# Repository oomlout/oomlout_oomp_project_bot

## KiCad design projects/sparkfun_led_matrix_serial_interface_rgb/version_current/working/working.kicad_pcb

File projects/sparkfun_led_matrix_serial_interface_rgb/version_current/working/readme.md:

# OOMP Project  
## LED_Matrix_Serial_Interface_RGB  by sparkfun  
  
oomp key: oomp_projects_flat_sparkfun_led_matrix_serial_interface_rgb  
(snippet of original readme)  
  
LED Matrix Serial Interface-RGB  
===============================  
  
[    
*LED Matrix - Serial Interface RGB (COM-00760)*](https://www.sparkfun.com/products/760)  
  
This is a large sized RGB LED matrix with a backpack that has been designed to take SPI serial input and display any graphics you pass it.  
  
Repository Contents  
-------------------  
* **/Firmware** - Any firmware that the part ships with,   
* **/Hardware** - All Eagle design files (.brd, .sch, .STL)  

License Information  
-------------------  
The hardware is released under [Creative Commons Share-alike 3.0](http://creativecommons.org/licenses/by-sa/3.0/).    
All other code is open source so please feel free to do anything you want with it; you buy me a beer if you use this and we meet someday ([Beerware license](http://en.wikipedia.org/wiki/Beerware)).  

  full source readme at [readme_src.md](readme_src.md)  
  
source repo at: [https://github.com/sparkfun/LED_Matrix_Serial_Interface_RGB](https://github.com/sparkfun/LED_Matrix_Serial_Interface_RGB)  
## Board  

## Schematic  

[schematic pdf](working_schematic.pdf)  
## Images

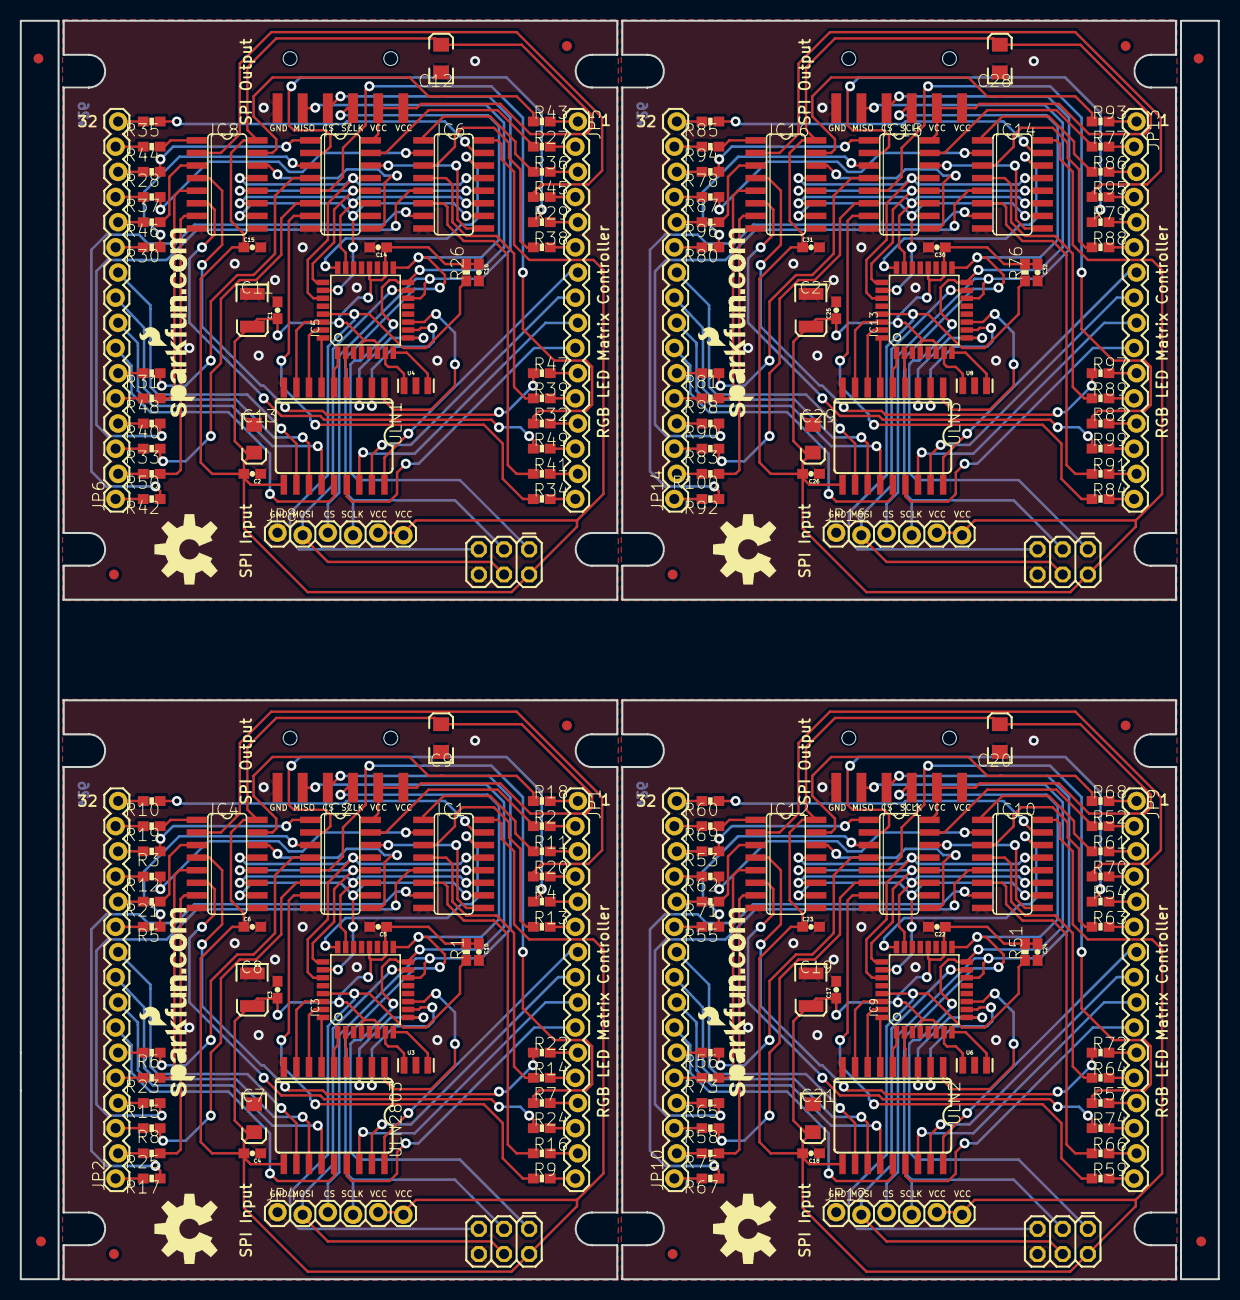
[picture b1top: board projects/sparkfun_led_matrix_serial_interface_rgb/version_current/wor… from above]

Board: 2 copper layers, 120.9 x 127.0 mm, 196 parts (0 on the bottom side), 320 nets.

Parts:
C1, C2, C3, C4, C17, C18, C25, C26: 0.1uf; 0603-CAP
C5, C6, C10, C14, C15, C16, C22, C23, C24, C30, C31, C32: 0.1uF; 0603-CAP
C7, C9, C12, C13, C20, C21, C28, C29: 10uF; EIA3216
C8, C11, C19, C27: 47uF; EIA3528
E$1, E$2, E$3, E$4: FIDUCIAL-1X2
IC1, IC2, IC4, IC6, IC7, IC8, IC10, IC11, IC12, IC14, IC15, IC16: 74LS595D; SO16
IC3, IC5, IC9, IC13: AVR-MEGA8-AI; TQFP32-08
JP1, JP2, JP5, JP6, JP9, JP10, JP13, JP14: M16LOCK; 1X16_LOCK
JP3, JP7, JP11, JP15: 1X06-SMD
JP4, JP8, JP12, JP16: 1X06_LOCK
LOGO1, LOGO2, LOGO3, LOGO4: OSHW-LOGOL; OSHW-LOGO-L
R1, R26, R51, R76: 10k; 0603-RES
R2, R3, R4, R5, R6, R7, R8, R9, R10, R11, R12, R13, R14, R15, R16, R17, R18, R19, R20, R21, R22, R23, R24, R25, R27, R28, R29, R30, R31, R32, R33, R34, R35, R36, R37, R38, R39, R40, R41, R42, R43, R44, R45, R46, R47, R48, R49, R50, R52, R53, R54, R55, R56, R57, R58, R59, R60, R61, R62, R63, R64, R65, R66, R67, R68, R69, R70, R71, R72, R73, R74, R75, R77, R78, R79, R80, R81, R82, R83, R84, R85, R86, R87, R88, R89, R90, R91, R92, R93, R94, R95, R96, R97, R98, R99, R100: 100; 0603-RES
U1, U2, U5, U7: AVR_SPI_PRG_6PTH; 2X3
U3, U4, U6, U8: 16 MHz; RESONATOR-SMD
U$1, U$2, U$3, U$4, U$6, U$7, U$10, U$11: FIDUCIAL1X2; FIDUCIAL-1X2
U$5, U$8, U$9, U$12: SFE-NEW-WEBLOGO
ULN1, ULN2, ULN3, ULN2803: SO18L

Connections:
B1: JP1.1, R18.2
B2: JP2.15, R19.2
B3: JP1.4, R20.2
B4: JP2.12, R21.2
B5: JP1.11, R22.2
B6: JP2.5, R23.2
B7: JP1.14, R24.2
B8: JP2.2, R25.2
B9: JP5.1, R43.2
B10: JP6.15, R44.2
B11: JP5.4, R45.2
B12: JP6.12, R46.2
B13: JP5.11, R47.2
B14: JP6.5, R48.2
B15: JP5.14, R49.2
B16: JP6.2, R50.2
B17: JP9.1, R68.2
B18: JP10.15, R69.2
B19: JP9.4, R70.2
B20: JP10.12, R71.2
B21: JP9.11, R72.2
B22: JP10.5, R73.2
B23: JP9.14, R74.2
B24: JP10.2, R75.2
B25: JP13.1, R93.2
B26: JP14.15, R94.2
B27: JP13.4, R95.2
B28: JP14.12, R96.2
B29: JP13.11, R97.2
B30: JP14.5, R98.2
B31: JP13.14, R99.2
B32: JP14.2, R100.2
CS: IC3.14, JP3.4, JP4.3
CS1: IC5.14, JP7.4, JP8.3
CS2: IC9.14, JP11.4, JP12.3
CS3: IC13.14, JP15.4, JP16.3
G1: JP1.2, R2.2
G2: JP2.14, R3.2
G3: JP1.5, R4.2
G4: JP2.11, R5.2
G5: JP2.6, R6.2
G6: JP1.13, R7.2
G7: JP2.3, R8.2
G8: JP1.16, R9.2
G9: JP5.2, R27.2
G10: JP6.14, R28.2
G11: JP5.5, R29.2
G12: JP6.11, R30.2
G13: JP6.6, R31.2
G14: JP5.13, R32.2
G15: JP6.3, R33.2
G16: JP5.16, R34.2
G17: JP9.2, R52.2
G18: JP10.14, R53.2
G19: JP9.5, R54.2
G20: JP10.11, R55.2
G21: JP10.6, R56.2
G22: JP9.13, R57.2
G23: JP10.3, R58.2
G24: JP9.16, R59.2
G25: JP13.2, R77.2
G26: JP14.14, R78.2
G27: JP13.5, R79.2
G28: JP14.11, R80.2
G29: JP14.6, R81.2
G30: JP13.13, R82.2
G31: JP14.3, R83.2
G32: JP13.16, R84.2
GND: C3.2, C4.1, C5.2, C6.2, C7.C, C8.C, C9.C, C10.2, IC1.8, IC2.8, IC3.3, IC3.5, IC3.21, IC4.8, JP3.6, JP4.1, U2.6, U3.2, ULN2803.9
GND1: C1.2, C2.1, C11.C, C12.C, C13.C, C14.2, C15.2, C16.2, IC5.3, IC5.5, IC5.21, IC6.8, IC7.8, IC8.8, JP7.6, JP8.1, U1.6, U4.2, ULN1.9
GND2: C17.2, C18.1, C19.C, C20.C, C21.C, C22.2, C23.2, C24.2, IC9.3, IC9.5, IC9.21, IC10.8, IC11.8, IC12.8, JP11.6, JP12.1, U5.6, U6.2, ULN2.9
GND3: C25.2, C26.1, C27.C, C28.C, C29.C, C30.2, C31.2, C32.2, IC13.3, IC13.5, IC13.21, IC14.8, IC15.8, IC16.8, JP15.6, JP16.1, U7.6, U8.2, ULN3.9
MISO: IC3.16, JP3.5, U2.1
MISO1: IC5.16, JP7.5, U1.1
MISO2: IC9.16, JP11.5, U5.1
MISO3: IC13.16, JP15.5, U7.1
MOSI: IC3.15, JP4.2, U2.4
MOSI1: IC5.15, JP8.2, U1.4
MOSI2: IC9.15, JP12.2, U5.4
MOSI3: IC13.15, JP16.2, U7.4
unnamed: IC3.7, U3.1
unnamed: IC3.8, U3.3
unnamed: IC6.15, R35.1
unnamed: IC6.1, R36.1
unnamed: IC6.2, R37.1
unnamed: IC6.3, R38.1
unnamed: IC6.4, R39.1
unnamed: IC6.5, R40.1
unnamed: IC6.6, R41.1
unnamed: IC6.7, R42.1
unnamed: IC1.9, IC2.14
unnamed: IC1.15, R10.1
unnamed: IC1.1, R11.1
unnamed: IC1.2, R12.1
unnamed: IC1.3, R13.1
unnamed: IC2.9, IC4.14
unnamed: IC7.15, R27.1
unnamed: IC1.4, R14.1
unnamed: IC1.5, R15.1
unnamed: IC1.6, R16.1
unnamed: IC1.7, R17.1
unnamed: IC2.15, R2.1
unnamed: IC2.1, R3.1
unnamed: IC2.2, R4.1
unnamed: IC2.3, R5.1
unnamed: IC2.4, R6.1
unnamed: IC2.5, R7.1
unnamed: IC2.6, R8.1
unnamed: IC2.7, R9.1
unnamed: IC7.1, R28.1
unnamed: IC7.2, R29.1
unnamed: IC4.15, R18.1
unnamed: IC4.1, R19.1
unnamed: IC4.2, R20.1
unnamed: IC4.3, R21.1
unnamed: IC4.4, R22.1
unnamed: IC4.5, R23.1
unnamed: IC4.6, R24.1
unnamed: IC4.7, R25.1
unnamed: IC7.3, R30.1
unnamed: IC7.4, R31.1
unnamed: IC7.5, R32.1
unnamed: IC7.6, R33.1
unnamed: IC7.7, R34.1
unnamed: IC8.15, R43.1
unnamed: IC8.1, R44.1
unnamed: IC8.2, R45.1
unnamed: IC8.3, R46.1
unnamed: IC8.4, R47.1
unnamed: IC8.5, R48.1
unnamed: IC8.6, R49.1
unnamed: IC8.7, R50.1
unnamed: IC6.9, IC7.14
unnamed: IC7.9, IC8.14
unnamed: IC5.7, U4.1
unnamed: IC5.8, U4.3
unnamed: IC10.15, R60.1
unnamed: IC10.1, R61.1
unnamed: IC10.2, R62.1
unnamed: IC10.3, R63.1
unnamed: IC10.4, R64.1
unnamed: IC10.5, R65.1
unnamed: IC10.6, R66.1
unnamed: IC10.7, R67.1
unnamed: IC11.15, R52.1
unnamed: IC11.1, R53.1
unnamed: IC11.2, R54.1
unnamed: IC11.3, R55.1
unnamed: IC11.4, R56.1
unnamed: IC11.5, R57.1
unnamed: IC11.6, R58.1
unnamed: IC11.7, R59.1
unnamed: IC12.15, R68.1
unnamed: IC12.1, R69.1
unnamed: IC12.2, R70.1
unnamed: IC12.3, R71.1
unnamed: IC12.4, R72.1
unnamed: IC12.5, R73.1
unnamed: IC12.6, R74.1
unnamed: IC12.7, R75.1
unnamed: IC10.9, IC11.14
unnamed: IC11.9, IC12.14
unnamed: IC9.7, U6.1
unnamed: IC9.8, U6.3
unnamed: IC14.15, R85.1
unnamed: IC14.1, R86.1
unnamed: IC14.2, R87.1
unnamed: IC14.3, R88.1
unnamed: IC14.4, R89.1
unnamed: IC14.5, R90.1
unnamed: IC14.6, R91.1
unnamed: IC14.7, R92.1
unnamed: IC15.15, R77.1
unnamed: IC15.1, R78.1
unnamed: IC15.2, R79.1
unnamed: IC15.3, R80.1
unnamed: IC15.4, R81.1
unnamed: IC15.5, R82.1
unnamed: IC15.6, R83.1
unnamed: IC15.7, R84.1
unnamed: IC16.15, R93.1
unnamed: IC16.1, R94.1
unnamed: IC16.2, R95.1
unnamed: IC16.3, R96.1
unnamed: IC16.4, R97.1
unnamed: IC16.5, R98.1
unnamed: IC16.6, R99.1
unnamed: IC16.7, R100.1
unnamed: IC14.9, IC15.14
unnamed: IC15.9, IC16.14
unnamed: IC13.7, U8.1
unnamed: IC13.8, U8.3
R1: JP2.16, R10.2
R2: JP1.3, R11.2
R3: JP2.13, R12.2
R4: JP1.6, R13.2
R5: JP1.12, R14.2
R6: JP2.4, R15.2
R7: JP1.15, R16.2
R8: JP2.1, R17.2
R9: JP6.16, R35.2
R10: JP5.3, R36.2
R11: JP6.13, R37.2
R12: JP5.6, R38.2
R13: JP5.12, R39.2
R14: JP6.4, R40.2
R15: JP5.15, R41.2
R16: JP6.1, R42.2
R17: JP10.16, R60.2
R18: JP9.3, R61.2
R19: JP10.13, R62.2
R20: JP9.6, R63.2
R21: JP9.12, R64.2
R22: JP10.4, R65.2
R23: JP9.15, R66.2
R24: JP10.1, R67.2
R25: JP14.16, R85.2
R26: JP13.3, R86.2
R27: JP14.13, R87.2
R28: JP13.6, R88.2
R29: JP13.12, R89.2
R30: JP14.4, R90.2
R31: JP13.15, R91.2
R32: JP14.1, R92.2
ROW1: JP2.10, ULN2803.11
ROW2: JP2.9, ULN2803.12
ROW3: JP2.8, ULN2803.13
ROW4: JP2.7, ULN2803.14
ROW5: JP1.10, ULN2803.15
ROW6: JP1.9, ULN2803.16
ROW7: JP1.8, ULN2803.17
ROW8: JP1.7, ULN2803.18
ROW9: JP5.7, ULN1.18
ROW10: JP5.8, ULN1.17
ROW11: JP5.9, ULN1.16
ROW12: JP5.10, ULN1.15
ROW13: JP6.7, ULN1.14
ROW14: JP6.8, ULN1.13
ROW15: JP6.9, ULN1.12
ROW16: JP6.10, ULN1.11
ROW17: JP9.7, ULN2.18
ROW18: JP9.8, ULN2.17
ROW19: JP9.9, ULN2.16
ROW20: JP9.10, ULN2.15
ROW21: JP10.7, ULN2.14
ROW22: JP10.8, ULN2.13
ROW23: JP10.9, ULN2.12
ROW24: JP10.10, ULN2.11
ROW25: JP13.7, ULN3.18
ROW26: JP13.8, ULN3.17
ROW27: JP13.9, ULN3.16
ROW28: JP13.10, ULN3.15
ROW29: JP14.7, ULN3.14
ROW30: JP14.8, ULN3.13
ROW31: JP14.9, ULN3.12
ROW32: JP14.10, ULN3.11
ROW_1: IC3.30, ULN2803.8
ROW_2: IC3.31, ULN2803.7
ROW_3: IC3.32, ULN2803.6
ROW_4: IC3.1, ULN2803.5
ROW_5: IC3.2, ULN2803.4
ROW_6: IC3.9, ULN2803.3
ROW_7: IC3.10, ULN2803.2
ROW_8: IC3.11, ULN2803.1
ROW_9: IC5.11, ULN1.1
ROW_10: IC5.10, ULN1.2
ROW_11: IC5.9, ULN1.3
ROW_12: IC5.2, ULN1.4
ROW_13: IC5.1, ULN1.5
ROW_14: IC5.32, ULN1.6
ROW_15: IC5.31, ULN1.7
ROW_16: IC5.30, ULN1.8
ROW_17: IC9.11, ULN2.1
ROW_18: IC9.10, ULN2.2
ROW_19: IC9.9, ULN2.3
ROW_20: IC9.2, ULN2.4
ROW_21: IC9.1, ULN2.5
ROW_22: IC9.32, ULN2.6
ROW_23: IC9.31, ULN2.7
ROW_24: IC9.30, ULN2.8
ROW_25: IC13.11, ULN3.1
ROW_26: IC13.10, ULN3.2
ROW_27: IC13.9, ULN3.3
ROW_28: IC13.2, ULN3.4
ROW_29: IC13.1, ULN3.5
ROW_30: IC13.32, ULN3.6
ROW_31: IC13.31, ULN3.7
ROW_32: IC13.30, ULN3.8
RST: IC3.29, R1.1, U2.5
RST1: IC5.29, R26.1, U1.5
RST2: IC9.29, R51.1, U5.5
RST3: IC13.29, R76.1, U7.5
SCK: IC3.17, JP3.3, JP4.4, U2.3
SCK1: IC5.17, JP7.3, JP8.4, U1.3
SCK2: IC9.17, JP11.3, JP12.4, U5.3
SCK3: IC13.17, JP15.3, JP16.4, U7.3
SR_CLEAR: IC1.10, IC2.10, IC3.26, IC4.10
SR_CLEAR1: IC5.26, IC6.10, IC7.10, IC8.10
SR_CLEAR2: IC9.26, IC10.10, IC11.10, IC12.10
SR_CLEAR3: IC13.26, IC14.10, IC15.10, IC16.10
SR_DATA: IC1.14, IC3.24
SR_DATA1: IC5.24, IC6.14
SR_DATA2: IC9.24, IC10.14
SR_DATA3: IC13.24, IC14.14
SR_EN: IC1.13, IC2.13, IC3.27, IC4.13
SR_EN1: IC5.27, IC6.13, IC7.13, IC8.13
SR_EN2: IC9.27, IC10.13, IC11.13, IC12.13
SR_EN3: IC13.27, IC14.13, IC15.13, IC16.13
SR_LATCH: IC1.12, IC2.12, IC3.25, IC4.12
SR_LATCH1: IC5.25, IC6.12, IC7.12, IC8.12
SR_LATCH2: IC9.25, IC10.12, IC11.12, IC12.12
SR_LATCH3: IC13.25, IC14.12, IC15.12, IC16.12
SR_SCK: IC1.11, IC2.11, IC3.23, IC4.11
SR_SCK1: IC5.23, IC6.11, IC7.11, IC8.11
SR_SCK2: IC9.23, IC10.11, IC11.11, IC12.11
SR_SCK3: IC13.23, IC14.11, IC15.11, IC16.11
VCC: C3.1, C4.2, C5.1, C6.1, C7.A, C8.A, C9.A, C10.1, IC1.16, IC2.16, IC3.4, IC3.6, IC3.18, IC3.20, IC4.16, JP3.1, JP3.2, JP4.5, JP4.6, R1.2, U2.2, ULN2803.10
VCC1: C1.1, C2.2, C11.A, C12.A, C13.A, C14.1, C15.1, C16.1, IC5.4, IC5.6, IC5.18, IC5.20, IC6.16, IC7.16, IC8.16, JP7.1, JP7.2, JP8.5, JP8.6, R26.2, U1.2, ULN1.10
VCC2: C17.1, C18.2, C19.A, C20.A, C21.A, C22.1, C23.1, C24.1, IC9.4, IC9.6, IC9.18, IC9.20, IC10.16, IC11.16, IC12.16, JP11.1, JP11.2, JP12.5, JP12.6, R51.2, U5.2, ULN2.10
VCC3: C25.1, C26.2, C27.A, C28.A, C29.A, C30.1, C31.1, C32.1, IC13.4, IC13.6, IC13.18, IC13.20, IC14.16, IC15.16, IC16.16, JP15.1, JP15.2, JP16.5, JP16.6, R76.2, U7.2, ULN3.10

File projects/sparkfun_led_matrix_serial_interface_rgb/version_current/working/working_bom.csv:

Row,Description,Part,References,Value,Footprint,Quantity Per PCB,Status,Datasheet
1,,CAP0603-CAP,C3 C4 C5 C6 C10,0.1uf,0603-CAP,5, ,
2,,CAP_POL1206,C7 C9,10uF,EIA3216,2, ,
3,,CAP_POL3528,C8,47uF,EIA3528,1, ,
4,,FRAME-LEDGER,FRAME1,FRAME-LEDGER,CREATIVE_COMMONS,1, ,
5,,74595D,IC1 IC2 IC4,74595D,SO16,3, ,
6,,AVR-MEGA8-AI,IC3,AVR-MEGA8-AI,TQFP32-08,1, ,
7,,SparkFun-Connectors_M06LOCK,JP4,M06LOCK,1X06_LOCK,1, ,
8,,M06SMD,JP3,M06SMD,1X06-SMD,1, ,
9,,M16LOCK,JP1 JP2,M16LOCK,1X16_LOCK,2, ,
10,,OSHW-LOGOL,LOGO1,OSHW-LOGOL,OSHW-LOGO-L,1, ,
11,,RESISTOR0603-RES,R2 R3 R4 R5 R6 R7 R8 R9 R10 R11 R12 R13 R14 R15 R16 R17 R18 R19 R20 R21 R22 R23 R24 R25,100,0603-RES,24, ,
12,,RESISTOR0603-RES,R1,10k,0603-RES,1, ,
13,,AVR_SPI_PRG_6PTH,U2,AVR_SPI_PRG_6PTH,2X3,1, ,
14,,RESONATORSMD,U3,RESONATORSMD,RESONATOR-SMD,1, ,
15,,REVISION,U$2,REVISION,REVISION,1, ,
16,,ULN2803SOICW,ULN2803,ULN2803SOICW,SO18L,1, ,





Project info:
Schematic:,working
Variant:,default
Revision:,
Date:,2023-08-06_12-56-04
KiCad Version:,7.0.6-7.0.6~ubuntu22.04.1
Statistics:
Component Groups:,16
Component Count:,47 (0 SMD/ 0 THT)
Fitted Components:,47 (0 SMD/ 0 THT)
Number of PCBs:,1
Total Components:,47

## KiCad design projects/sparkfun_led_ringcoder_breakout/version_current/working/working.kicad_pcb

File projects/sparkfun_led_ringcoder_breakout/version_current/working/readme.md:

# OOMP Project  
## LED_RingCoder_Breakout  by sparkfun  
  
oomp key: oomp_projects_flat_sparkfun_led_ringcoder_breakout  
(snippet of original readme)  
  
**NOTE:** *This product has been retired from our catalog. If you are looking for more up-to-date info, please check out some of these resources to see how other users are still hacking and improving on this product.*  
* *[SparkFun Forum](https://forum.sparkfun.com/)*  
* *[Comments Here on GitHub](https://github.com/sparkfun/LED_RingCoder_Breakout/issues)*  
* *[IRC Channel](https://www.sparkfun.com/news/263)*  
  
LED RingCoder Breakout - RGB  
============================  

[    
*LED RingCoder Breakout-RGB (BOB-11040)*](https://www.sparkfun.com/products/11040)  
  
This breakout board gives you a pretty slick interface for rotary input. This board uses two 8-bit shift registers to control a circular  
LED bargraph which can be used to indicate the virtual position of a rotary encoder.   
  
Repository Contents  
-------------------  
* **/Firmware** - Example Arduino sketch to use with this board   
* **/Hardware** - All Eagle design files (.brd, .sch)  
* **/Production** - Test bed files and production panel files  
  
Product Versions  
----------------  
  
Compatible with the following rotary encoder and LED bar graphs:   
  
* [COM-10982](https://www.sparkfun.com/products/10982)- RGB rotary encoder-illuminated.  
* [COM-10591](https://www.sparkfun.com/products/retired/10591)- Circular LED Bargraphs - Green  
* [COM-10592](https://www.sparkfun.com/products/retired/10592)- Circular LED Bargraphs - Blue  
* [COM-1  
  full source readme at [readme_src.md](readme_src.md)  
  
source repo at: [https://github.com/sparkfun/LED_RingCoder_Breakout](https://github.com/sparkfun/LED_RingCoder_Breakout)  
## Board  

## Schematic  

[schematic pdf](working_schematic.pdf)  
## Images

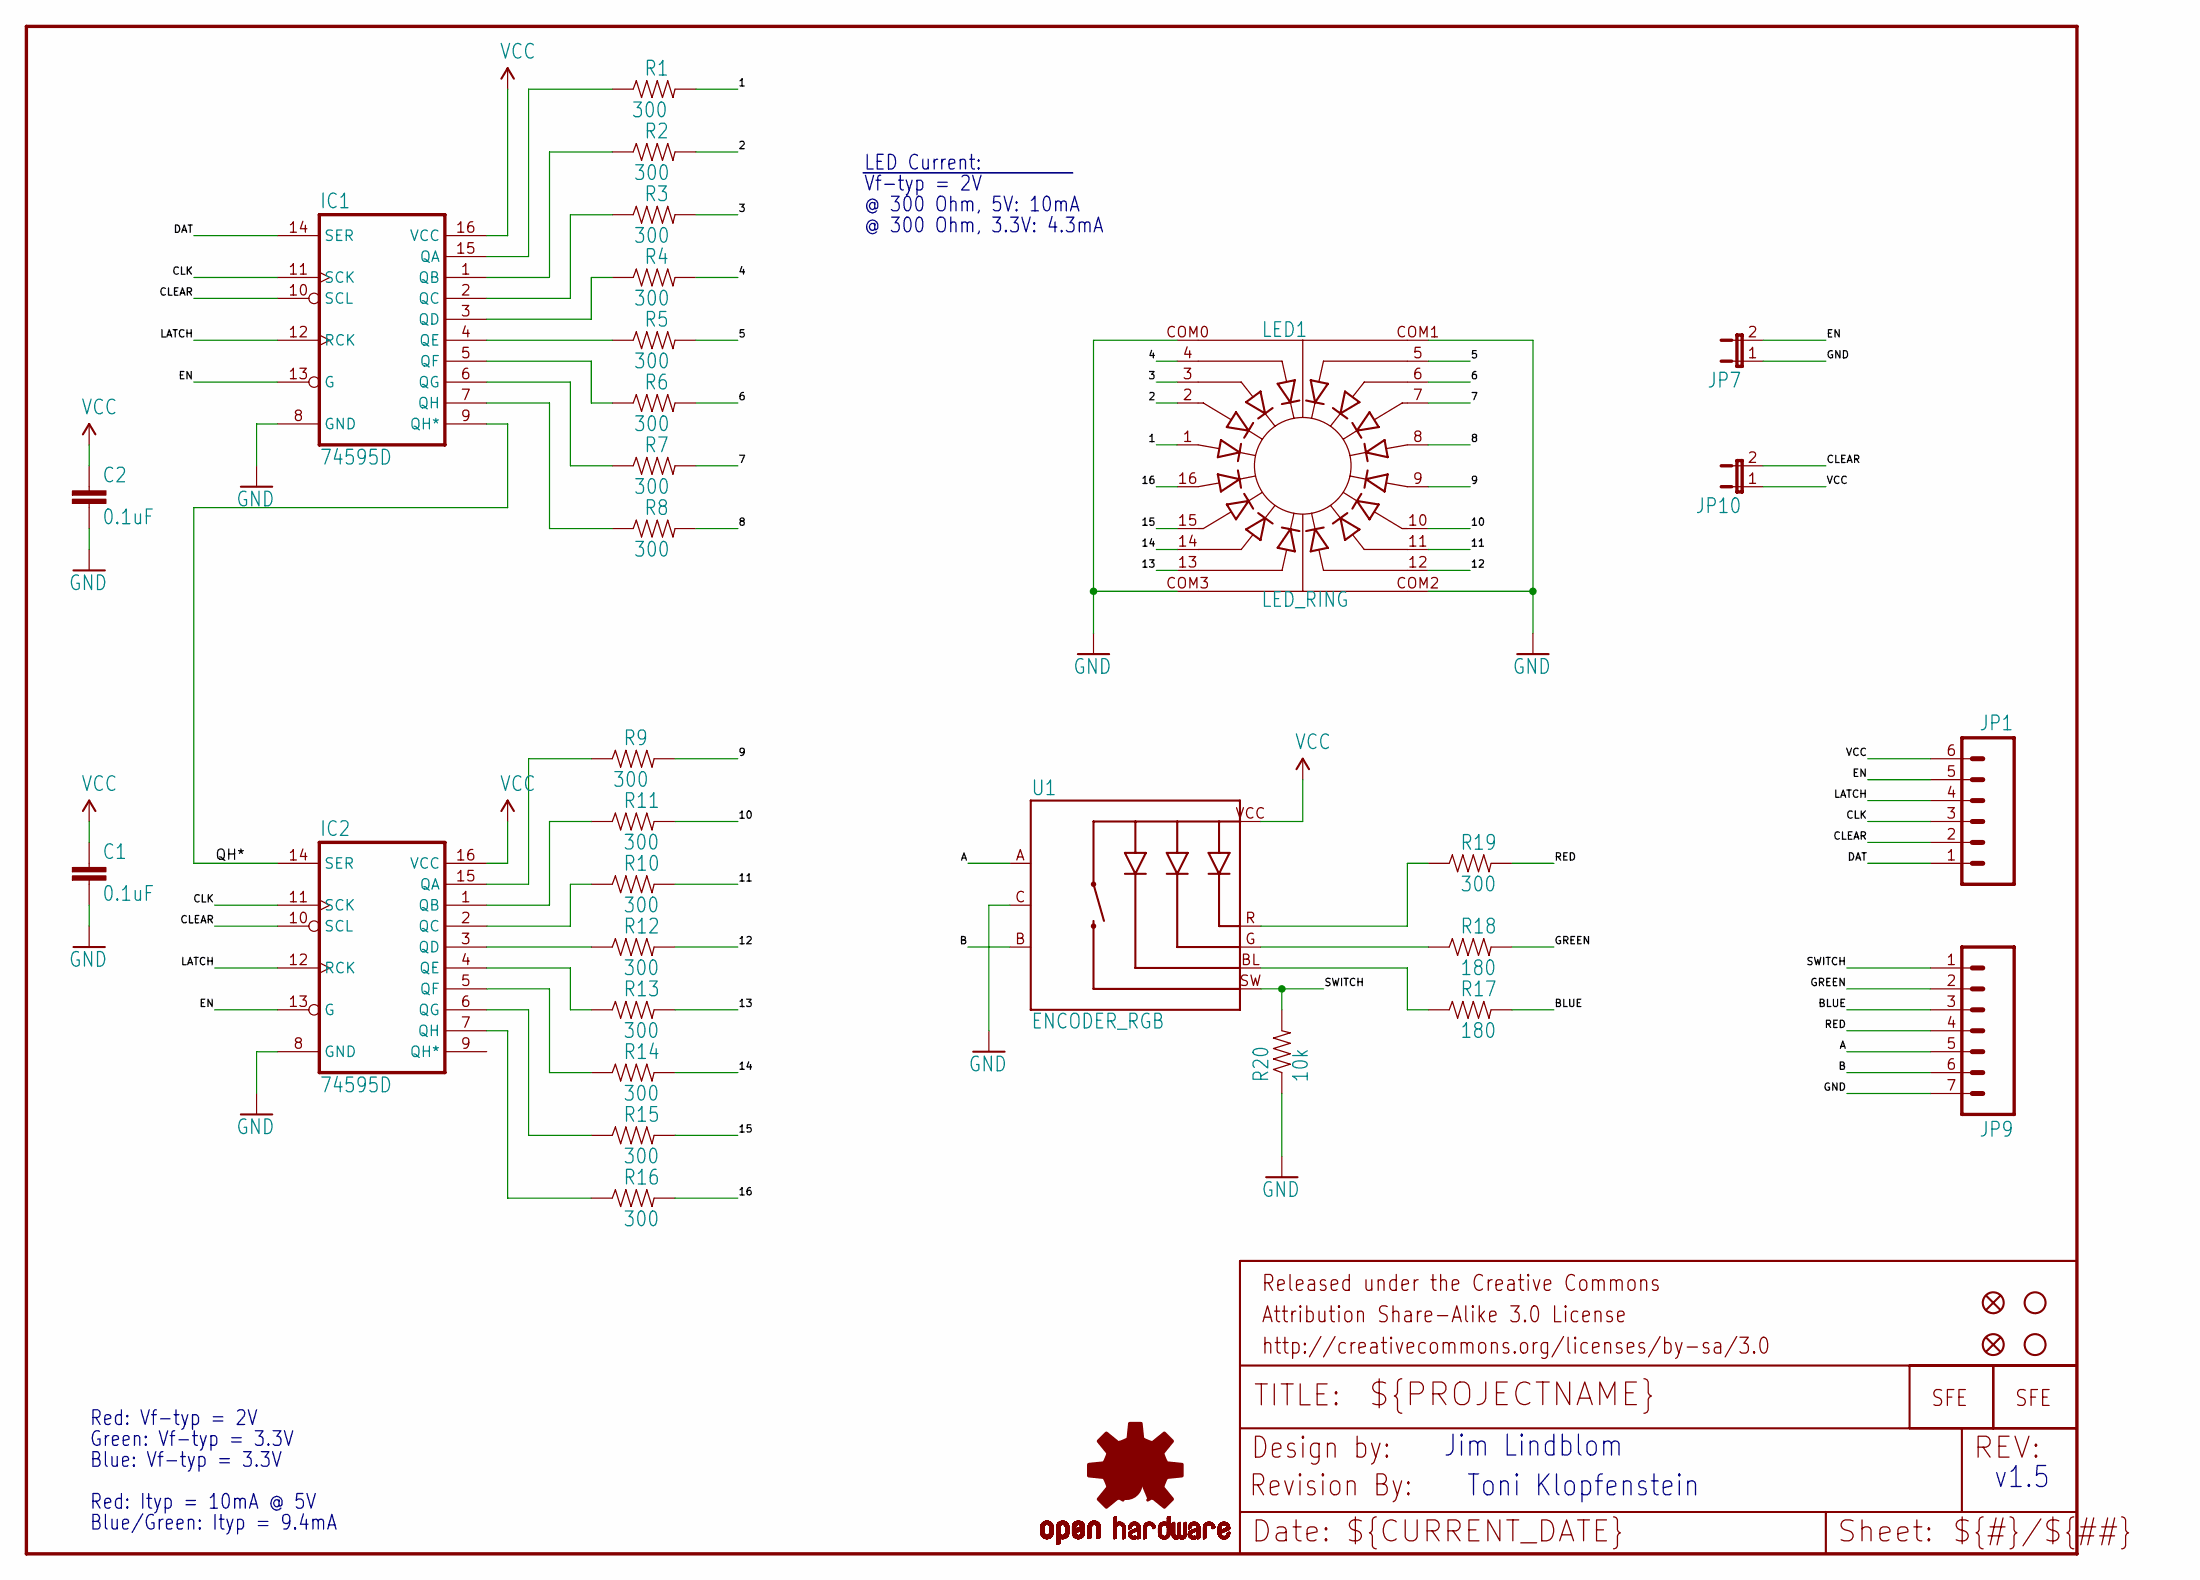
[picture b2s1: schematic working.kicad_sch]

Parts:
C1, C2: 0.1uF; 0603-CAP
FRAME1: FRAME-LETTER; CREATIVE_COMMONS
IC1, IC2: 74595D; SO16
JP1: M06SIP; 1X06
JP2: LOGO-SFENW2; SFE-NEW-WEB
JP3, JP4: STAND-OFF
JP5, JP8: FIDUCIAL1X2.5; FIDUCIAL-1X2.5
JP6: LOGO-SFESK; SFE-LOGO-FLAME
JP7, JP10: JUMPER-2SMD-NC; SJ_2S
JP9: M07; 1X07
LED1: LED_RING
R1, R2, R3, R4, R5, R6, R7, R8, R9, R10, R11, R12, R13, R14, R15, R16, R19: 300; 0603-RES
R17, R18: 180; 0603-RES
R20: 10k; 0603-RES
U1: ENCODER_RGB; ENCODER_LED_RGB
U$1: REVISION
U$2: OSHW-LOGOS; OSHW-LOGO-S

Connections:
1: LED1.1, R1.2
2: LED1.2, R2.2
3: LED1.3, R3.2
4: LED1.4, R4.2
5: LED1.5, R5.2
6: LED1.6, R6.2
7: LED1.7, R7.2
8: LED1.8, R8.2
9: LED1.9, R9.2
10: LED1.10, R11.2
11: LED1.11, R10.2
12: LED1.12, R12.2
13: LED1.13, R13.2
14: LED1.14, R14.2
15: LED1.15, R15.2
16: LED1.16, R16.2
A: JP9.5, U1.A
B: JP9.6, U1.B
BLUE: JP9.3, R17.2
CLEAR: IC1.10 (SCL), IC2.10 (SCL), JP1.2, JP10.2
CLK: IC1.11 (SCK), IC2.11 (SCK), JP1.3
DAT: IC1.14 (SER), JP1.1
EN: IC1.13 (G), IC2.13 (G), JP1.5, JP7.2
GND: C1.2, C2.2, IC1.8 (GND), IC2.8 (GND), JP7.1, JP9.7, LED1.COM0, LED1.COM1, LED1.COM2, LED1.COM3, R20.1, U1.C
GREEN: JP9.2, R18.2
LATCH: IC1.12 (RCK), IC2.12 (RCK), JP1.4
LED-B: R17.1, U1.BL
LED-G: R18.1, U1.G
LED-R: R19.1, U1.R
unnamed: IC1.15 (QA), R1.1
unnamed: IC1.1 (QB), R2.1
unnamed: IC1.2 (QC), R3.1
unnamed: IC1.3 (QD), R4.1
unnamed: IC1.4 (QE), R5.1
unnamed: IC1.5 (QF), R6.1
unnamed: IC1.6 (QG), R7.1
unnamed: IC1.7 (QH), R8.1
unnamed: IC2.15 (QA), R9.1
unnamed: IC2.1 (QB), R11.1
unnamed: IC2.2 (QC), R10.1
unnamed: IC2.3 (QD), R12.1
unnamed: IC2.4 (QE), R13.1
unnamed: IC2.5 (QF), R14.1
unnamed: IC2.6 (QG), R15.1
unnamed: IC2.7 (QH), R16.1
QH*: IC1.9 (QH*), IC2.14 (SER)
RED: JP9.4, R19.2
SWITCH: JP9.1, R20.2, U1.SW
VCC: C1.1, C2.1, IC1.16 (VCC), IC2.16 (VCC), JP1.6, JP10.1, U1.VCC

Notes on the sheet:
LED Current:
Jim Lindblom
Toni Klopfenstein
Green: Vf-typ = 3.3V
Blue/Green: Ityp = 9.4mA
Vf-typ = 2V
Blue: Vf-typ = 3.3V
v1.5
Red: Ityp = 10mA @ 5V
Red: Vf-typ = 2V
@ 300 Ohm, 3.3V: 4.3mA
@ 300 Ohm, 5V: 10mA

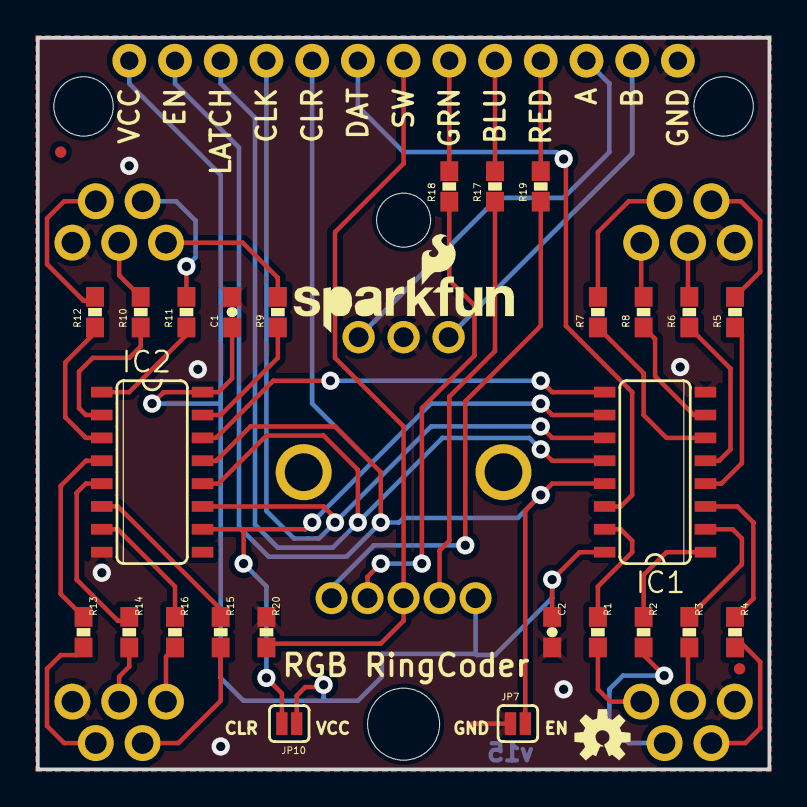
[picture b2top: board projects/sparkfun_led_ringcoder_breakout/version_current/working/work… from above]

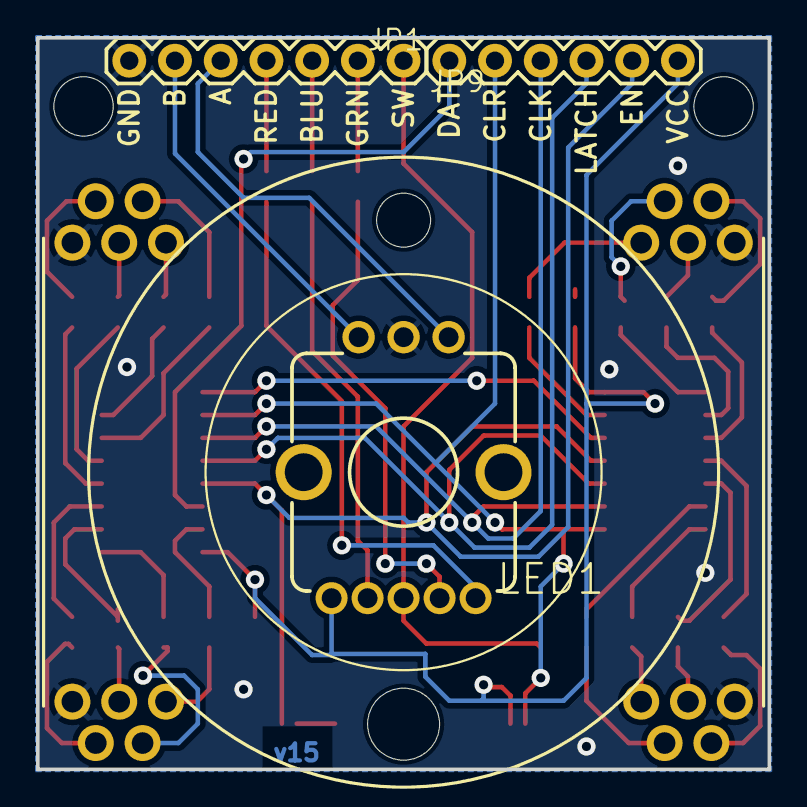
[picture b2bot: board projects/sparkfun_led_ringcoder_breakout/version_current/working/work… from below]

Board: 2 copper layers, 40.6 x 40.6 mm, 39 parts (6 on the bottom side), 49 nets.

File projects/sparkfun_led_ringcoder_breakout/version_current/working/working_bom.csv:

Row,Description,Part,References,Value,Footprint,Quantity Per PCB,Status,Datasheet
1,,0.1UF-25V(+80/-20%)(0603),C1 C2,0.1uF,0603-CAP,2, ,
2,,FRAME-LETTER,FRAME1,FRAME-LETTER,CREATIVE_COMMONS,1, ,
3,,74595D,IC1 IC2,74595D,SO16,2, ,
4,,JUMPER-2SMD-NC,JP7 JP10,JUMPER-2SMD-NC,SJ_2S,2, ,
5,,LOGO-SFENW2,JP2,LOGO-SFENW2,SFE-NEW-WEB,1, ,
6,,LOGO-SFESK,JP6,LOGO-SFESK,SFE-LOGO-FLAME,1, ,
7,,M06SIP,JP1,M06SIP,1X06,1, ,
8,,M07,JP9,M07,1X07,1, ,
9,,STAND-OFF,JP3 JP4,STAND-OFF,STAND-OFF,2, ,
10,,LED_RING,LED1,LED_RING,LED_RING,1, ,
11,,180OHM1/10W1%(0603),R17 R18,180,0603-RES,2, ,
12,,300OHM-1/10W-1%(0603),R1 R2 R3 R4 R5 R6 R7 R8 R9 R10 R11 R12 R13 R14 R15 R16 R19,300,0603-RES,17, ,
13,,10KOHM1/10W1%(0603)0603,R20,10k,0603-RES,1, ,
14,,ENCODER_RGB,U1,ENCODER_RGB,ENCODER_LED_RGB,1, ,
15,,OSHW-LOGOS,U$2,OSHW-LOGOS,OSHW-LOGO-S,1, ,
16,,REVISION,U$1,REVISION,REVISION,1, ,





Project info:
Schematic:,working
Variant:,default
Revision:,
Date:,2023-08-06_12-56-04
KiCad Version:,7.0.6-7.0.6~ubuntu22.04.1
Statistics:
Component Groups:,16
Component Count:,37 (0 SMD/ 0 THT)
Fitted Components:,37 (0 SMD/ 0 THT)
Number of PCBs:,1
Total Components:,37

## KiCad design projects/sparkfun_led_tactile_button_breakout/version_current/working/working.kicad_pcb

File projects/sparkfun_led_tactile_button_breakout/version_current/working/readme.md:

# LED_Tactile_Button_Breakout by sparkfun  
This is a harvested standardized copy of a project from github.  
The original project can be found at:  
https://github.com/sparkfun/LED_Tactile_Button_Breakout  
Please consult that link for additional, details, files, and license information.  
Note: It was auto harvested and if the original repo had more than one board file or anything out of the ordinary the files here are likely not representative.

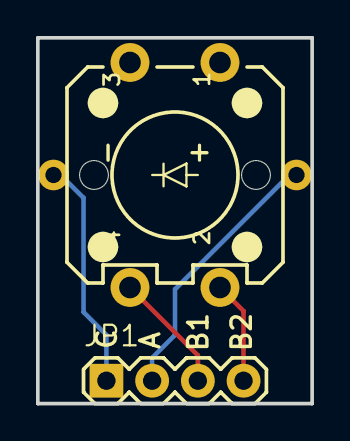
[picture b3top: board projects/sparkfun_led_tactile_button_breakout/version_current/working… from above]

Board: 2 copper layers, 15.2 x 20.3 mm, 4 parts (1 on the bottom side), 4 nets.

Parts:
JP1: 1X04
JP3: LOGO-SFESK; SFE-LOGO-FLAME
S1: Switch; TACTILE-PTH-LED-12MM
U$1: CREATIVE_COMMONS

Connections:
unnamed: JP1.4, S1.2
unnamed: JP1.3, S1.4
unnamed: JP1.2, S1.A
unnamed: JP1.1, S1.C

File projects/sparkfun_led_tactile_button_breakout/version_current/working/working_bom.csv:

Row,Description,Part,References,Value,Footprint,Quantity Per PCB,Status,Datasheet
1,,FRAME-LETTER,FRAME1,FRAME-LETTER,CREATIVE_COMMONS,1, ,
2,,M04PTH,JP1,M04PTH,1X04,1, ,
3,,SWITCH-MOMENTARY-LEDPTH,S1,SWITCH-MOMENTARY-LEDPTH,TACTILE-PTH-LED-12MM,1, ,





Project info:
Schematic:,working
Variant:,default
Revision:,
Date:,2023-08-06_12-56-04
KiCad Version:,7.0.6-7.0.6~ubuntu22.04.1
Statistics:
Component Groups:,3
Component Count:,3 (0 SMD/ 0 THT)
Fitted Components:,3 (0 SMD/ 0 THT)
Number of PCBs:,1
Total Components:,3

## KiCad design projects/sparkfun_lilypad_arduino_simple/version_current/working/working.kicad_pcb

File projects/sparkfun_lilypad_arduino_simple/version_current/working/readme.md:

# OOMP Project  
## LilyPad_Arduino_Simple  by sparkfun  
  
oomp key: oomp_projects_flat_sparkfun_lilypad_arduino_simple  
(snippet of original readme)  
  
LilyPad Arduino Simple  
======================  

[*LilyPad Arduino Simple Board (DEV-10274)*](https://www.sparkfun.com/products/10274)  
  
This LilyPad board is smaller than the LilyPad Main Board, with fewer pins. However, it does have a   
built-in power supply socket, and an on/off switch.   
  
Repository Contents  
-------------------  
  
* **/Hardware** - All Eagle design files (.brd, .sch, .STL)  
* **/Production** - Test bed files and production panel files  
  
License Information  
-------------------  
The hardware is released under [Creative Commons ShareAlike 4.0 International](https://creativecommons.org/licenses/by-sa/4.0/).  
The code is beerware; if you see me (or any other SparkFun employee) at the local, and you've found our code helpful, please buy us a round!  
  
Distributed as-is; no warranty is given.  
  
  full source readme at [readme_src.md](readme_src.md)  
  
source repo at: [https://github.com/sparkfun/LilyPad_Arduino_Simple](https://github.com/sparkfun/LilyPad_Arduino_Simple)  
## Board  

## Schematic  

[schematic pdf](working_schematic.pdf)  
## Images

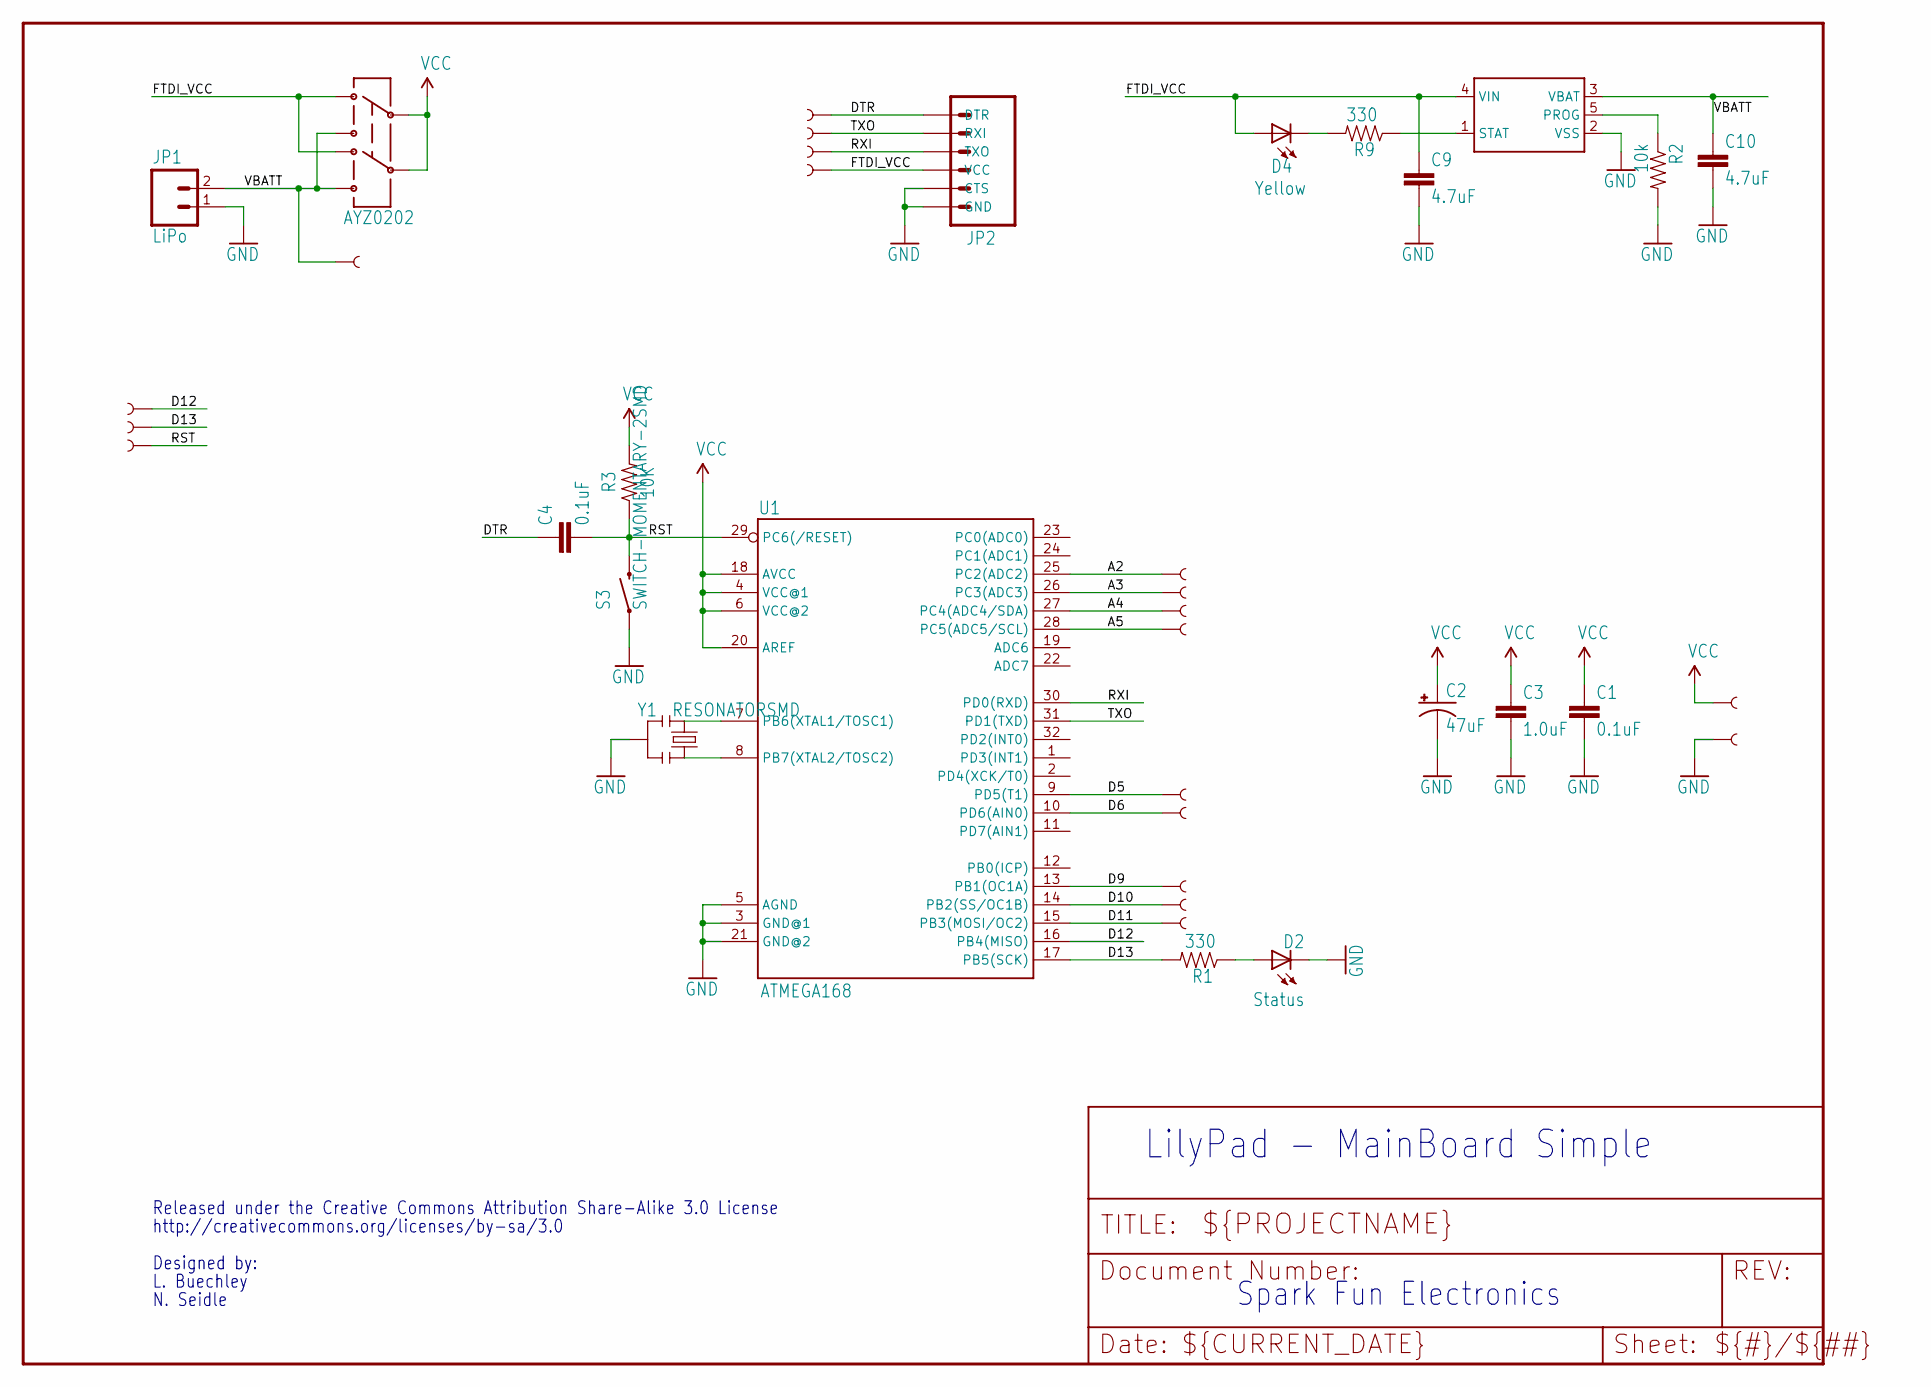
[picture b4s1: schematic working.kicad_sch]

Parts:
A2/16, A3/17, A4/18, A5/19: SEWTAP9; PETAL-LONG-1-2SIDE
C1, C4: 0.1uF; 0402-CAP
C2: 47uF; EIA3528
C3: 1.0uF; 0402-CAP
C9, C10: 4.7uF; 0402-CAP
D2: Status; LED-0603
D4: Yellow; LED-0603
JP1: LiPo; JST-2-SMD
JP2: ARDUINO_SERIAL_PROGRAMSMD; 1X06-SMD
PP-MISO0: TEST-POINT3X5; PAD.03X.05
PP-RST0: TEST-POINT3X5; PAD.03X.05
PP-SCK0: TEST-POINT3X5; PAD.03X.05
R1, R9: 330; 0402-RES
R2: 10k; 0402-RES
R3: 10K; 0402-RES
S2: AYZ0202
S3: SWITCH-MOMENTARY-2SMD; TACTILE_SWITCH_SMD
TP-DTR0: TEST-POINT3X5; PAD.03X.05
TP-FTDI_VCC0: TEST-POINT3X5; PAD.03X.05
TP-RX0: TEST-POINT3X5; PAD.03X.05
TP-TX0: TEST-POINT3X5; PAD.03X.05
TP-VBATT0: TEST-POINT3X5; PAD.03X.05
U1: ATMEGA168; TQFP32-08
U2: MCP73831; SOT23-5
U$4, U$35, U$37, U$39, U$41, U$43, U$45: SEWTAP9; PETAL-LONG-1-2SIDE
Y1: RESONATORSMD; RESONATOR-SMD

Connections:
A2: A2/16.1, U1.25 (PC2(ADC2))
A3: A3/17.1, U1.26 (PC3(ADC3))
A4: A4/18.1, U1.27 (PC4(ADC4/SDA))
A5: A5/19.1, U1.28 (PC5(ADC5/SCL))
D5: U1.9 (PD5(T1)), U$41.1
D6: U1.10 (PD6(AIN0)), U$35.1
D9: U1.13 (PB1(OC1A)), U$37.1
D10: U1.14 (PB2(SS/OC1B)), U$39.1
D11: U1.15 (PB3(MOSI/OC2)), U$4.1
D12: PP-MISO0.P$1, U1.16 (PB4(MISO))
D13: PP-SCK0.P$1, R1.2, U1.17 (PB5(SCK))
DTR: C4.1, JP2.1 (DTR), TP-DTR0.P$1
FTDI_VCC: C9.1, D4.A, JP2.4 (VCC), S2.3 (1), S2.6 (4), TP-FTDI_VCC0.P$1, U2.4 (VIN)
GND: C1.2, C2.C (-), C3.2, C9.2, C10.2, D2.C, JP1.1, JP2.5 (CTS), JP2.6 (GND), R2.2, S3.1, U1.3 (GND@1), U1.5 (AGND), U1.21 (GND@2), U2.2 (VSS), U$43.1, Y1.2
unnamed: U1.7 (PB6(XTAL1/TOSC1)), Y1.1
unnamed: D2.A, R1.1
unnamed: U1.8 (PB7(XTAL2/TOSC2)), Y1.3
unnamed: D4.C, R9.2
PROG: R2.1, U2.5 (PROG)
RST: C4.2, PP-RST0.P$1, R3.1, S3.3 (2), U1.29 (PC6(/RESET))
RXI: JP2.3 (TXO), TP-RX0.P$1, U1.30 (PD0(RXD))
STAT: R9.1, U2.1 (STAT)
TXO: JP2.2 (RXI), TP-TX0.P$1, U1.31 (PD1(TXD))
VBATT: C10.1, JP1.2, S2.1 (3), S2.4 (6), TP-VBATT0.P$1, U2.3 (VBAT)
VCC: C1.1, C2.A (+), C3.1, R3.2, S2.2, S2.5, U1.4 (VCC@1), U1.6 (VCC@2), U1.18 (AVCC), U1.20 (AREF), U$45.1

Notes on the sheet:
N. Seidle
L. Buechley
Released under the Creative Commons Attribution Share-Alike 3.0 License
Spark Fun Electronics
http://creativecommons.org/licenses/by-sa/3.0
Designed by:
LilyPad - MainBoard Simple
